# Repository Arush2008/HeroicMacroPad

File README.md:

# Heroic MacroPad
Its a 9 key macropad with 2 rotatory switches which will be used to do different tasks like changing the britness, sound and some vs code shortcuts to make the work flow batter.

# Why I choose to make this 
I have been stugling using some of the features which waste a lot of time while I am doing stuff and those stuff make me less productive doing my work so I want to make a macropad and want it to be in my desk which will help me a lot and it looks soo cool as well when its on the desk. I am making my own customized which is more batter as I can customize all the buttons more detailed and can have the same number of buttons that I need.

# Things I need

| Qty | Name                          |
|-----|-------------------------------|
| 11  | 1N4148 diodes                 |
| 9   | Cherry MX switches            |
| 2   | EC11 rotary encoder           |
| 2   | EC11 knob                     |
| 1   | PCB                           |
| 1   | Seeed Studio XIAO RP2040      |
| 4   | M3 x 16mm screws              |
| 4   | M3 heatset inserts            |
| 9   | keycaps                       |
| 1   | Case top and bottom           |
| 4   | rubber feet                   |

# Images

## PCB        

## Shemetic       

## Full Macropad design     

## Backside of macropad     

## Bottom part     

## Top part

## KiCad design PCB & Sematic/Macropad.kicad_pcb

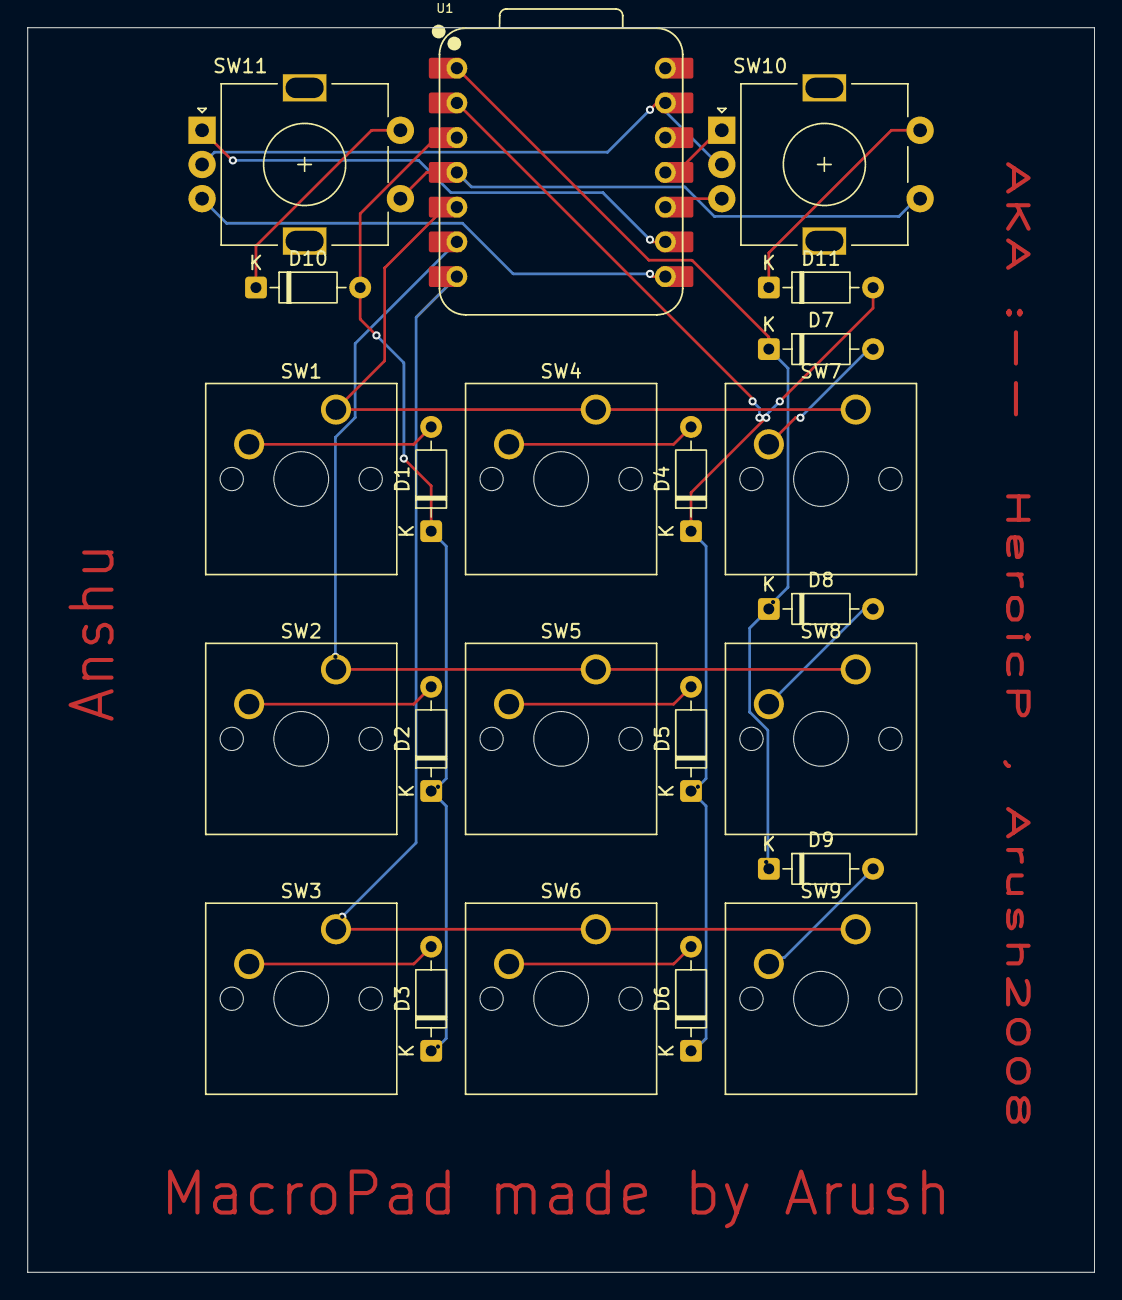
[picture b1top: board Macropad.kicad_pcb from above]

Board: 2 copper layers, 78.0 x 91.0 mm, 23 parts (0 on the bottom side), 23 nets.

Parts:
D1, D2, D3, D4, D5, D6, D7, D8, D9, D10, D11: 1N4148; D_DO-35_SOD27_P7.62mm_Horizontal
SW1, SW2, SW3, SW4, SW5, SW6, SW7, SW8, SW9: SW_Push_45deg; SW_Cherry_MX_1.00u_PCB
SW10, SW11: RotaryEncoder_Switch; RotaryEncoder_Alps_EC11E-Switch_Vertical_H20mm
U1: XIAO-RP2040-DIP

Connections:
GND: SW10.C, SW11.C, U1.13 (GND)
unnamed: D1.2 (A), SW1.2
unnamed: D1.1 (K), D2.1 (K), D3.1 (K), D10.2 (A), U1.3 (GPIO28/ADC2/A2)
unnamed: D2.2 (A), SW2.2
unnamed: D3.2 (A), SW3.2
unnamed: D4.2 (A), SW4.2
unnamed: D5.2 (A), SW5.2
unnamed: D6.2 (A), SW6.2
unnamed: D7.2 (A), SW7.2
unnamed: D7.1 (K), D8.1 (K), D9.1 (K), U1.1 (GPIO26/ADC0/A0)
unnamed: D8.2 (A), SW8.2
unnamed: D9.2 (A), SW9.2
unnamed: D10.1 (K), SW11.S2
unnamed: D4.1 (K), D5.1 (K), D6.1 (K), D11.2 (A), U1.2 (GPIO27/ADC1/A1)
unnamed: D11.1 (K), SW10.S2
unnamed: SW3.1, SW6.1, SW9.1, U1.7 (GPIO0/TX)
unnamed: SW11.B, U1.8 (GPIO1/RX)
unnamed: SW11.A, U1.9 (GPIO2/SCK)
unnamed: SW10.A, U1.11 (GPIO3/MOSI)
unnamed: SW10.B, U1.10 (GPIO4/MISO)
unnamed: SW1.1, SW4.1, SW7.1, U1.5 (GPIO6/SDA)
unnamed: SW2.1, SW5.1, SW8.1, U1.6 (GPIO7/SCL)
unnamed: SW10.S1, SW11.S1, U1.4 (GPIO29/ADC3/A3)

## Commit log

2025-07-13 Create Assets
2025-07-13 Rename Assets to NA
2025-07-13 Create l
2025-07-13 Create a
2025-07-13 Create fads
2025-07-14 Rename main.py to main.py
2025-07-14 Rename base.f3d to base.f3d
2025-07-14 Create fasdkjflkdsajfljk
2025-07-14 Create asadfasddf
2025-07-14 Final changes done
